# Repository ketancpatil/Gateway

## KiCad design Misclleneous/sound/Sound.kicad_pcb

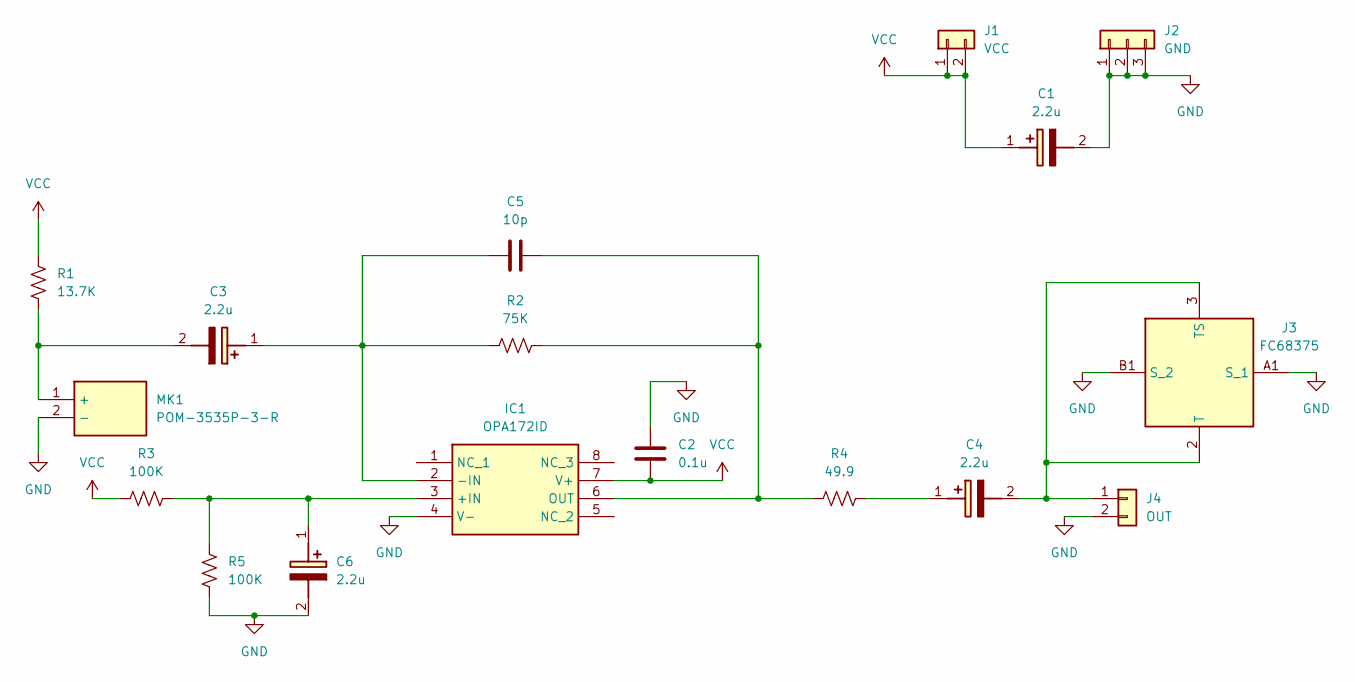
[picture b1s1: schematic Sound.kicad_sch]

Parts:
C1, C3, C4, C6: 2.2u; 293D225X9016A2TE3; Manufacturer_Part_Number 293D225X9016A2TE3; Mouser Part Number 74-293D225X9016A2TE3
C2: 0.1u; C_1206_3216Metric_Pad1.33x1.80mm_HandSolder
C5: 10p; C_1206_3216Metric_Pad1.33x1.80mm_HandSolder
IC1: OPA172ID; SOIC127P600X175-8N; Mouser Part Number 595-OPA172ID
J1: VCC; PinSocket_1x02_P2.54mm_Vertical
J2: GND; PinSocket_1x03_P2.54mm_Vertical
J3: FC68375; Manufacturer_Part_Number FC68375
J4: OUT; PinSocket_1x02_P2.54mm_Vertical
MK1: POM-3535P-3-R; POM3535P3R; Manufacturer_Part_Number POM-3535P-3-R; Mouser Part Number 665-POM-3535P-3-R
R1: 13.7K; R_1206_3216Metric_Pad1.30x1.75mm_HandSolder
R2: 75K; R_1206_3216Metric_Pad1.30x1.75mm_HandSolder
R3, R5: 100K; R_1206_3216Metric_Pad1.30x1.75mm_HandSolder
R4: 49.9; R_1206_3216Metric_Pad1.30x1.75mm_HandSolder

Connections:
GND: C1.2 (-), C2.2, C6.2 (-), IC1.4 (V-), J2.1, J2.2, J2.3, J3.A1 (S_1), J3.B1 (S_2), J4.2, MK1.2 (-), R5.1
unnamed: C3.1 (+), C5.2, IC1.2 (-IN), R2.1
unnamed: C3.2 (-), MK1.1 (+), R1.2
unnamed: C4.1 (+), R4.2
unnamed: C4.2 (-), J3.2 (T), J3.3 (TS), J4.1
unnamed: C6.1 (+), IC1.3 (+IN), R3.2, R5.2
unnamed: C5.1, IC1.6 (OUT), R2.2, R4.1
VCC: C1.1 (+), C2.1, IC1.7 (V+), J1.1, J1.2, R1.1, R3.1

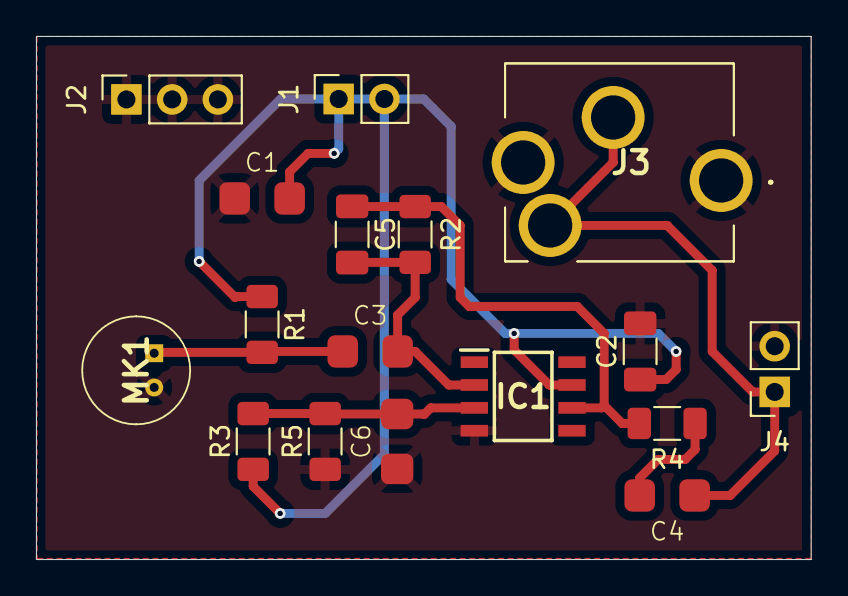
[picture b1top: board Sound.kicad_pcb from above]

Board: 2 copper layers, 43.0 x 29.1 mm, 17 parts (0 on the bottom side), 8 nets.

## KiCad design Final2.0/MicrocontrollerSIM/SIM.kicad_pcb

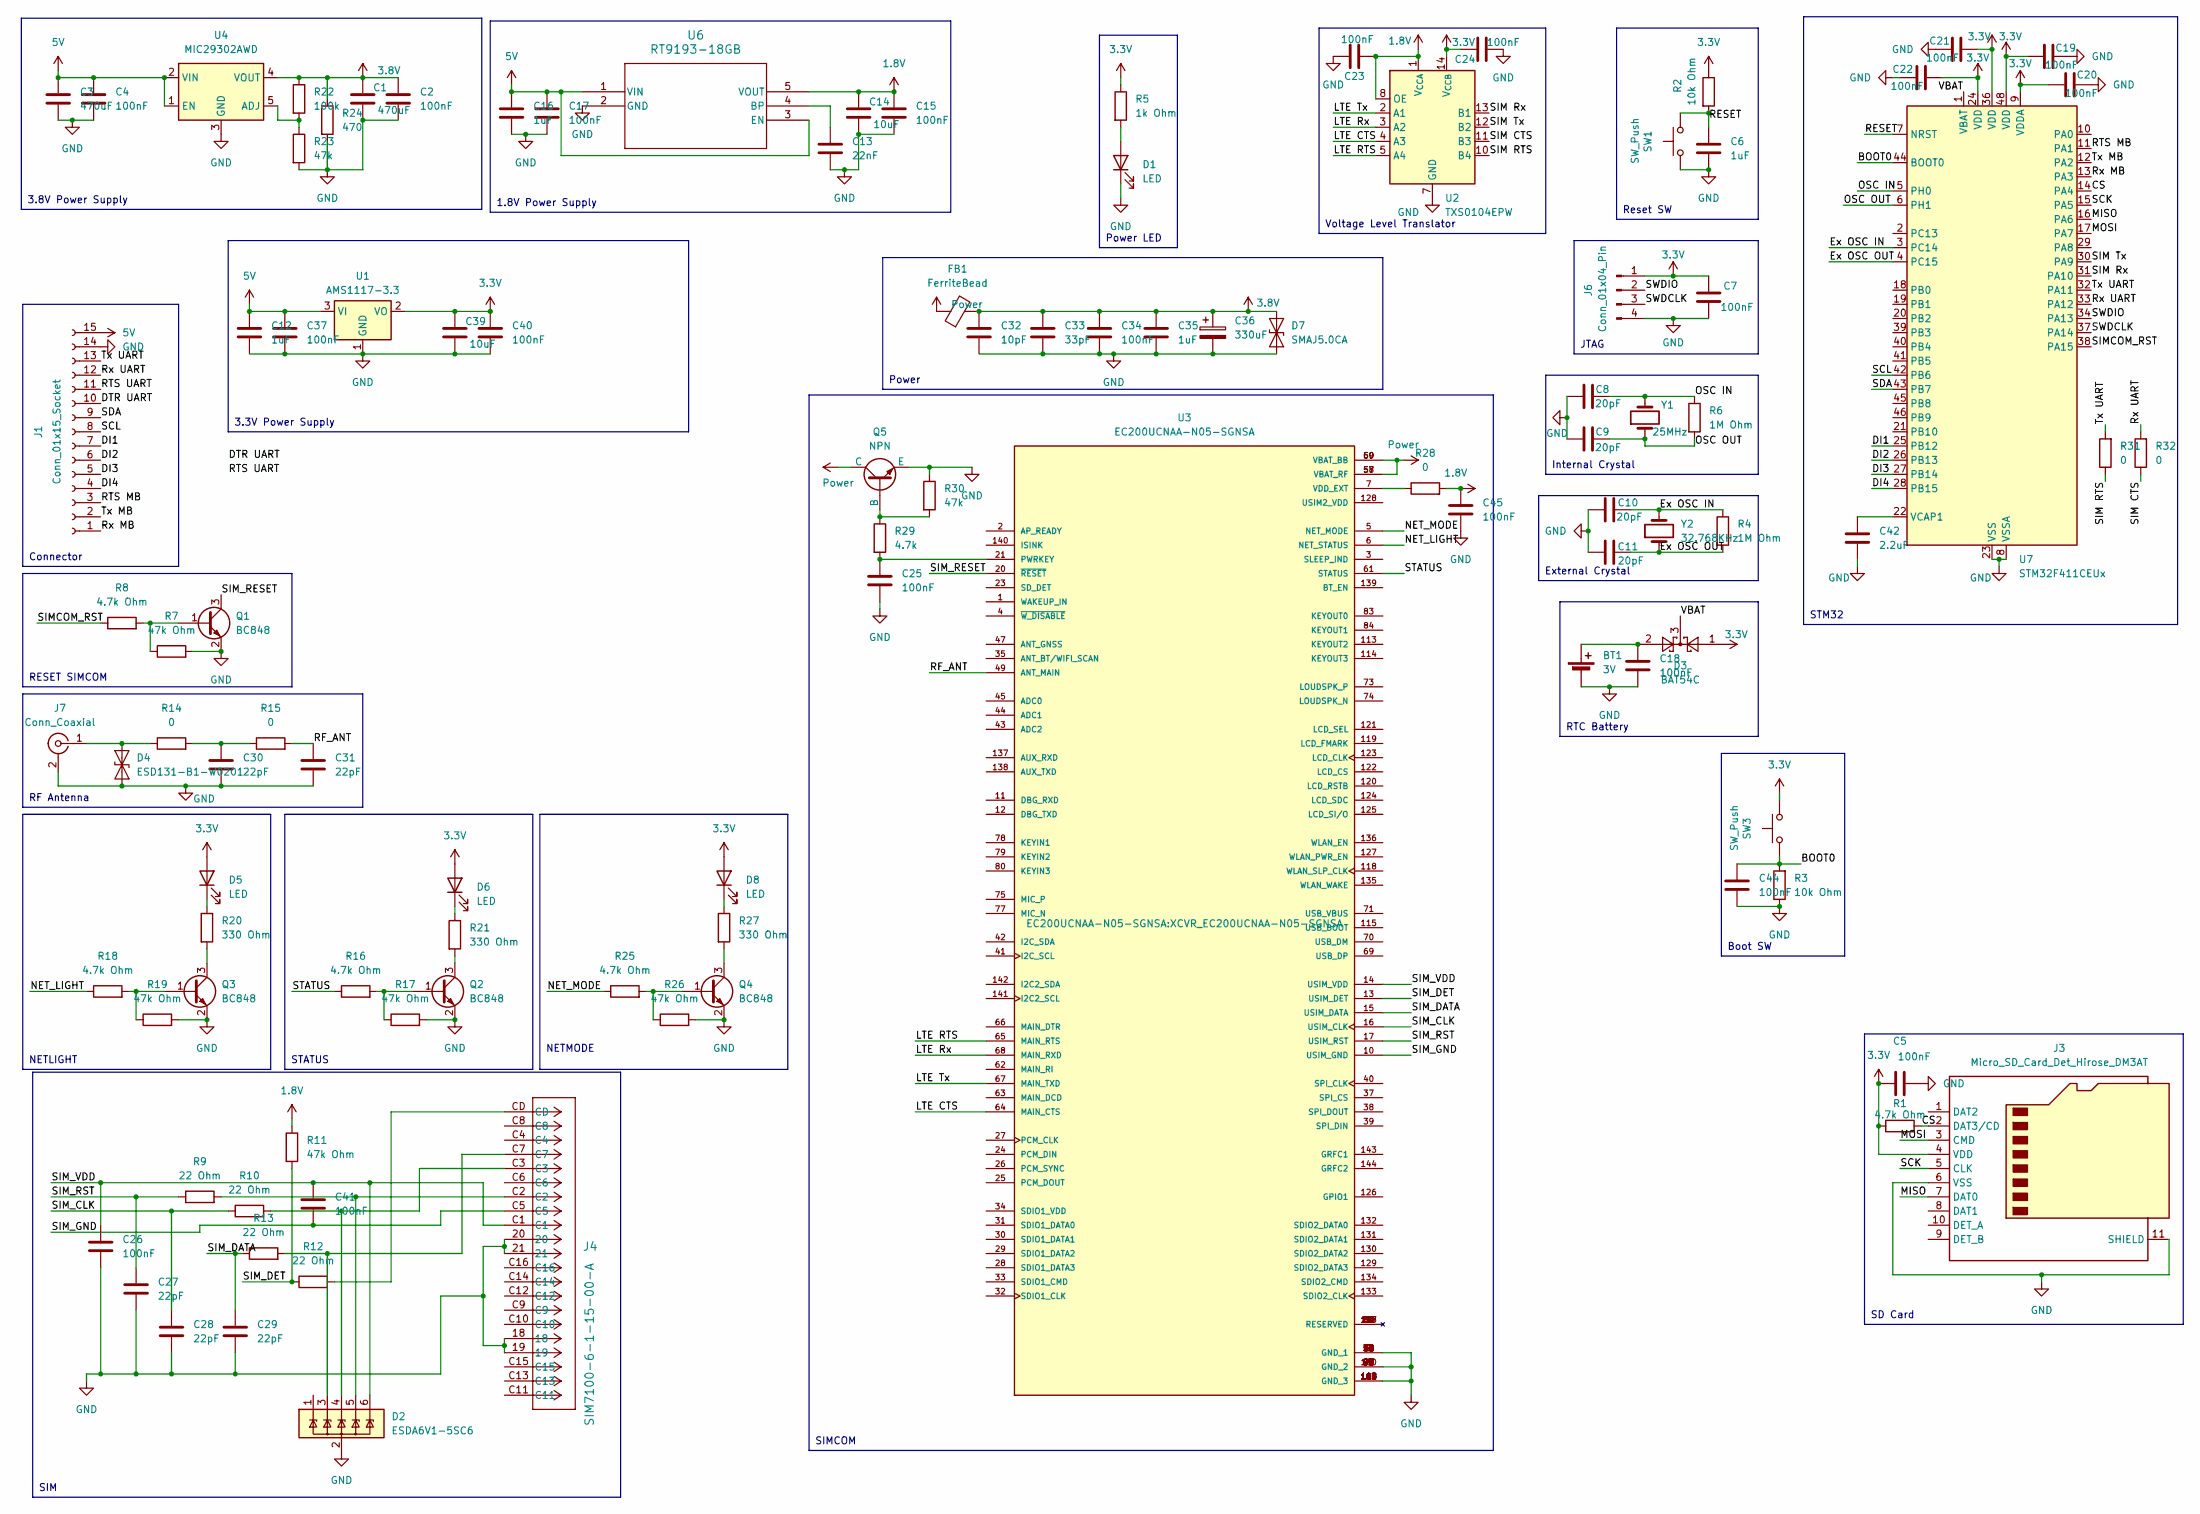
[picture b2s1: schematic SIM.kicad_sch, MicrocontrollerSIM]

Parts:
BT1: 3V; PinHeader_1x02_P2.54mm_Vertical
C1, C3: 470uF; CP_EIA-7260-15_AVX-R_Pad2.68x6.30mm_HandSolder
C2, C4, C5, C7, C15, C17, C18, C19, C20, C21, C22, C23, C24, C25, C26, C34, C37, C40, C41, C44, C45: 100nF; C_0805_2012Metric_Pad1.18x1.45mm_HandSolder
C6, C12, C16, C35: 1uF; C_0805_2012Metric_Pad1.18x1.45mm_HandSolder
C8, C9, C10, C11: 20pF; C_0805_2012Metric_Pad1.18x1.45mm_HandSolder
C13: 22nF; C_0805_2012Metric_Pad1.18x1.45mm_HandSolder
C14, C39: 10uF; C_0805_2012Metric_Pad1.18x1.45mm_HandSolder
C27, C28, C29, C30, C31: 22pF; C_0805_2012Metric_Pad1.18x1.45mm_HandSolder
C32: 10pF; C_0805_2012Metric_Pad1.18x1.45mm_HandSolder
C33: 33pF; C_0805_2012Metric_Pad1.18x1.45mm_HandSolder
C36: 330uF; CP_EIA-6032-15_Kemet-U
C42: 2.2uF; C_0805_2012Metric_Pad1.18x1.45mm_HandSolder
D1, D5, D6, D8: LED; D_0805_2012Metric_Pad1.15x1.40mm_HandSolder
D2: ESDA6V1-5SC6; SOT-23-6
D3: BAT54C; SOT-23
D4: ESD131-B1-W0201; Nexperia_DSN0603-2_0.6x0.3mm_P0.4mm
D7: SMAJ5.0CA; D_SMA
FB1: FerriteBead; Fuse_1206_3216Metric_Pad1.42x1.75mm_HandSolder
J1: Conn_01x15_Socket; PinHeader_1x15_P2.54mm_Vertical
J3: Micro_SD_Card_Det_Hirose_DM3AT; microSD_HC_Hirose_DM3AT-SF-PEJM5
J4: SIM7100-6-1-15-00-A; CONN21_-6-1-15-00-A_GCT
J6: Conn_01x04_Pin; PinSocket_1x04_P2.54mm_Vertical
J7: Conn_Coaxial; U.FL_Molex_MCRF_73412-0110_Vertical
Q1, Q2, Q3, Q4: BC848; SOT-23
Q5: NPN; SOT-23-3
R1, R8, R16, R18, R25: 4.7k Ohm; R_0805_2012Metric_Pad1.20x1.40mm_HandSolder
R2, R3: 10k Ohm; R_0805_2012Metric_Pad1.20x1.40mm_HandSolder
R4, R6: 1M Ohm; R_0805_2012Metric_Pad1.20x1.40mm_HandSolder
R5: 1k Ohm; R_0805_2012Metric_Pad1.20x1.40mm_HandSolder
R7, R11, R17, R19, R26: 47k Ohm; R_0805_2012Metric_Pad1.20x1.40mm_HandSolder
R9, R10, R12, R13: 22 Ohm; R_0805_2012Metric_Pad1.20x1.40mm_HandSolder
R14, R15, R28, R31, R32: 0; R_0805_2012Metric_Pad1.20x1.40mm_HandSolder
R20, R21, R27: 330 Ohm; R_0805_2012Metric_Pad1.20x1.40mm_HandSolder
R22: 100k; R_0805_2012Metric_Pad1.20x1.40mm_HandSolder
R23, R30: 47k; R_0805_2012Metric_Pad1.20x1.40mm_HandSolder
R24: 470; R_0805_2012Metric_Pad1.20x1.40mm_HandSolder
R29: 4.7k; R_0805_2012Metric_Pad1.20x1.40mm_HandSolder
SW1, SW3: SW_Push; SW_SPST_B3U-1000P
U1: AMS1117-3.3; SOT-223-3_TabPin2
U2: TXS0104EPW; TSSOP-14_4.4x5mm_P0.65mm
U3: EC200UCNAA-N05-SGNSA; XCVR_EC200UCNAA-N05-SGNSA; PARTREV 1.2
U4: MIC29302AWD; TO-252-5_TabPin3
U6: RT9193-18GB; SOT-23-5_RIT
U7: STM32F411CEUx; QFN-48-1EP_7x7mm_P0.5mm_EP5.6x5.6mm
Y1: 25MHz; Crystal_SMD_MicroCrystal_CC7V-T1A-2Pin_3.2x1.5mm
Y2: 32.768KHz; Crystal_SMD_2012-2Pin_2.0x1.2mm_HandSoldering

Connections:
1.8V: C14.1, C15.1, C23.2, C45.1, R11.1, R28.2, U2.1 (V_{CCA}), U2.8 (OE), U6.5 (VOUT)
3.3V: C5.1, C7.1, C19.1, C20.1, C21.2, C22.2, C24.1, C39.1, C40.1, D3.1, D5.2 (A), D6.2 (A), D8.2 (A), J3.4 (VDD), J6.1, R1.1, R2.1, R5.1, SW3.2, U1.2 (VO), U2.14 (V_{CCB}), U7.9 (VDDA), U7.24 (VDD), U7.36 (VDD), U7.48 (VDD)
3.8V: C1.1, C2.1, C32.1, C33.1, C34.1, C35.1, C36.1, D7.2 (A2), FB1.2, R22.1, R24.1, U4.4 (VOUT)
5V: C3.1, C4.1, C12.1, C16.1, C17.1, C37.1, J1.15, U1.3 (VI), U4.1 (EN), U4.2 (VIN), U6.1 (VIN), U6.3 (EN)
/BOOT0: C44.1, R3.2, SW3.1, U7.44 (BOOT0)
/CS: J3.2 (DAT3/CD), R1.2, U7.14 (PA4)
/DI1: J1.7, U7.25 (PB12)
/DI2: J1.6, U7.26 (PB13)
/DI3: J1.5, U7.27 (PB14)
/DI4: J1.4, U7.28 (PB15)
/DTR UART: J1.10
/Ex OSC IN: C10.2, R4.1, U7.3 (PC14), Y2.2
/Ex OSC OUT: C11.2, R4.2, U7.4 (PC15), Y2.1
/LTE CTS: U2.4 (A3), U3.64 (MAIN_CTS)
/LTE RTS: U2.5 (A4), U3.65 (MAIN_RTS)
/LTE Rx: U2.3 (A2), U3.68 (MAIN_RXD)
/LTE Tx: U2.2 (A1), U3.67 (MAIN_TXD)
/MISO: J3.7 (DAT0), U7.16 (PA6)
/MOSI: J3.3 (CMD), U7.17 (PA7)
/NET_LIGHT: R18.1, U3.6 (NET_STATUS)
/NET_MODE: R25.1, U3.5 (NET_MODE)
/OSC IN: C8.2, R6.1, U7.5 (PH0), Y1.2
/OSC OUT: C9.2, R6.2, U7.6 (PH1), Y1.1
/RESET: C6.1, R2.2, SW1.2, U7.7 (NRST)
/RF_ANT: C31.1, R15.2, U3.49 (ANT_MAIN)
/RTS MB: J1.3, U7.11 (PA1)
/RTS UART: J1.11
/Rx MB: J1.1, U7.13 (PA3)
/Rx UART: J1.12, R32.2, U7.33 (PA12)
/SCK: J3.5 (CLK), U7.15 (PA5)
/SCL: J1.8, U7.42 (PB6)
/SDA: J1.9, U7.43 (PB7)
/SIM CTS: R32.1, U2.11 (B3)
/SIM RTS: R31.1, U2.10 (B4)
/SIM Rx: U2.13 (B1), U7.31 (PA10)
/SIM Tx: U2.12 (B2), U7.30 (PA9)
/SIMCOM_RST: R8.1, U7.38 (PA15)
/SIM_CLK: C28.1, R10.1, U3.16 (USIM_CLK)
/SIM_DATA: C29.1, R13.1, U3.15 (USIM_DATA)
/SIM_DET: R11.2, R12.1, U3.13 (USIM_DET)
/SIM_GND: C41.2, J4.C5, U3.10 (USIM_GND)
/SIM_RESET: Q1.3 (C), U3.20 (~RESET)
/SIM_RST: C27.1, R9.1, U3.17 (USIM_RST)
/SIM_VDD: C26.1, C41.1, D2.6 (IO5), J4.C1, U3.14 (USIM_VDD)
/STATUS: R16.1, U3.61 (STATUS)
/SWDCLK: J6.3, U7.37 (PA14)
/SWDIO: J6.2, U7.34 (PA13)
/Tx MB: J1.2, U7.12 (PA2)
/Tx UART: J1.13, R31.2, U7.32 (PA11)
/VBAT: D3.3, U7.1 (VBAT)
GND: BT1.2 (-), C1.2, C2.2, C3.2, C4.2, C5.2, C6.2, C7.2, C8.1, C9.1, C10.1, C11.1, C12.2, C13.2, C14.2, C15.2, C16.2, C17.2, C18.2, C19.2, C20.2, C21.1, C22.1, C23.1, C24.2, C25.1, C26.2, C27.2, C28.2, C29.2, C30.2, C31.2, C32.2, C33.2, C34.2, C35.2, C36.2, C37.2, C39.2, C40.2, C42.2, C44.2, C45.2, D1.1 (K), D2.2 (GND), D4.2 (A2), D7.1 (A1), J1.14, J3.6 (VSS), J3.11 (SHIELD), J4.18, J4.19, J4.20, J4.21, J6.4, J7.2 (Ext), Q1.2 (E), Q2.2 (E), Q3.2 (E), Q4.2 (E), Q5.3 (E), R3.1, R7.2, R17.2, R19.2, R23.2, R24.2, R26.2, R30.1, SW1.1, U1.1 (GND), U2.7 (GND), U3.8 (GND_1), U3.9 (GND_1), U3.19 (GND_1), U3.22 (GND_1), U3.36 (GND_1), U3.46 (GND_1), U3.48 (GND_1), U3.50 (GND_1), U3.51 (GND_1), U3.52 (GND_1), U3.53 (GND_1), U3.54 (GND_1), U3.56 (GND_1), U3.72 (GND_1), U3.76 (GND_1), U3.85 (GND_2), U3.86 (GND_2), U3.87 (GND_2), U3.88 (GND_2), U3.89 (GND_2), U3.90 (GND_2), U3.91 (GND_2), U3.92 (GND_2), U3.93 (GND_2), U3.94 (GND_2), U3.95 (GND_2), U3.96 (GND_2), U3.97 (GND_2), U3.98 (GND_2), U3.99 (GND_2), U3.100 (GND_2), U3.101 (GND_3), U3.102 (GND_3), U3.103 (GND_3), U3.104 (GND_3), U3.105 (GND_3), U3.106 (GND_3), U3.107 (GND_3), U3.108 (GND_3), U3.109 (GND_3), U3.110 (GND_3), U3.111 (GND_3), U3.112 (GND_3), U4.3 (GND), U6.2 (GND), U7.8 (VSSA), U7.23 (VSS), U7.35 (VSS), U7.47 (VSS), U7.49 (VSS)
unnamed: BT1.1 (+), C18.1, D3.2
unnamed: C30.1, R14.2, R15.1
unnamed: D1.2 (A), R5.2
unnamed: D2.3 (IO2), J4.C7, R13.2
unnamed: D2.4 (IO3), J4.C3, R10.2
unnamed: D2.5 (IO4), J4.C2, R9.2
unnamed: D4.1 (A1), J7.1 (In), R14.1
unnamed: D5.1 (K), R20.1
unnamed: D6.1 (K), R21.1
unnamed: D8.1 (K), R27.1
unnamed: J4.CD, R12.2
unnamed: Q1.1 (B), R7.1, R8.2
unnamed: Q2.1 (B), R16.2, R17.1
unnamed: Q2.3 (C), R21.2
unnamed: Q3.1 (B), R18.2, R19.1
unnamed: Q3.3 (C), R20.2
unnamed: Q4.1 (B), R25.2, R26.1
unnamed: Q4.3 (C), R27.2
unnamed: Q5.2 (B), R29.1, R30.2
unnamed: C25.2, R29.2, U3.21 (PWRKEY)
unnamed: R28.1, U3.7 (VDD_EXT)
unnamed: R22.2, R23.1, U4.5 (ADJ)
unnamed: C13.1, U6.4 (BP)
unnamed: C42.1, U7.22 (VCAP1)
Power: FB1.1, Q5.1 (C), U3.57 (VBAT_RF), U3.58 (VBAT_RF), U3.59 (VBAT_BB), U3.60 (VBAT_BB)

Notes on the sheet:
1.8V Power Supply
Power LED
External Crystal
JTAG
SIMCOM
RF Antenna
3.3V Power Supply
Connector
Reset SW
NETLIGHT
Internal Crystal
STM32
RESET SIMCOM
SD Card
NETMODE
SIM
STATUS
Voltage Level Translator
Boot SW
RTC Battery
3.8V Power Supply
Power

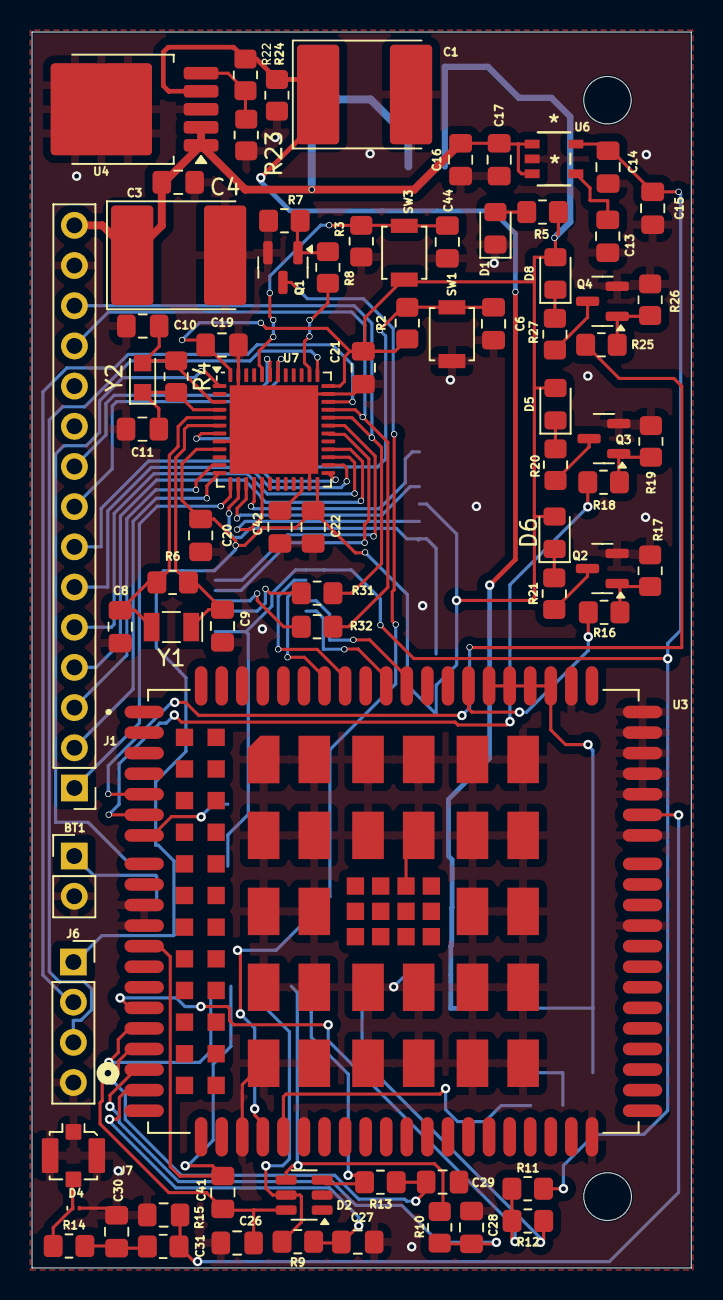
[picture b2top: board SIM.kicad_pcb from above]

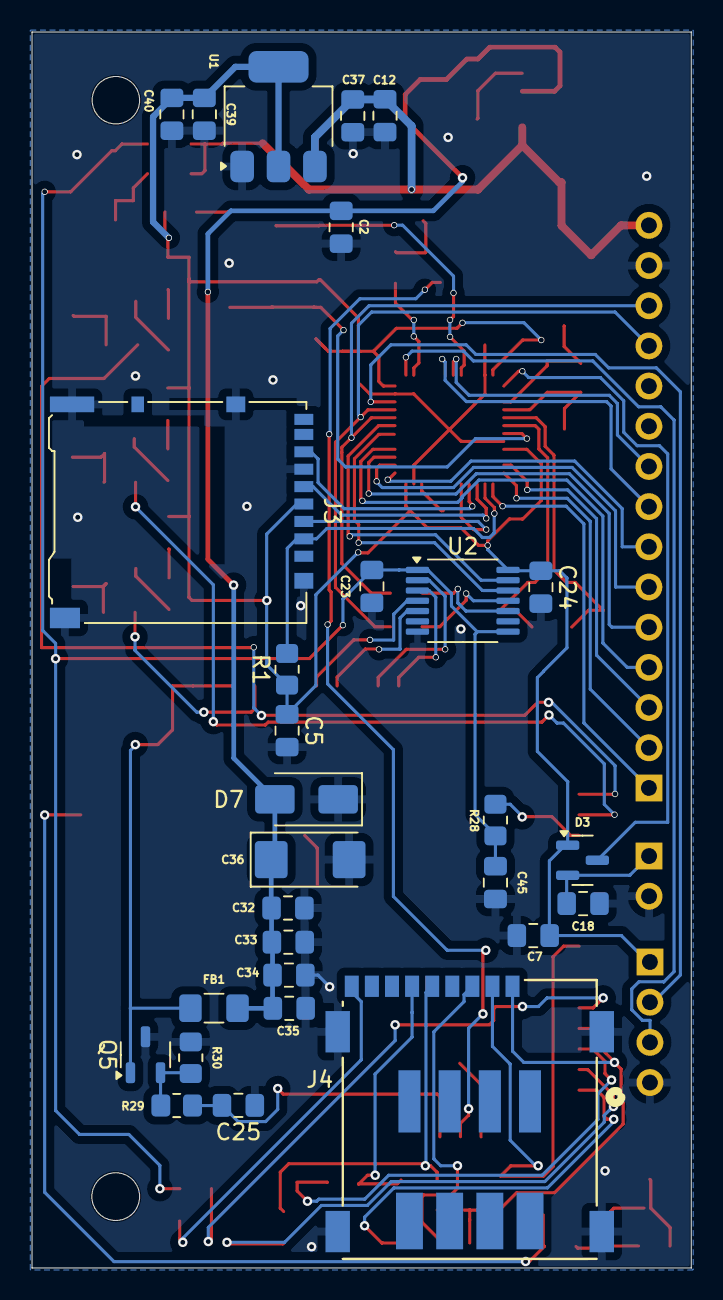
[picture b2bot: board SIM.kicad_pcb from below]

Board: 2 copper layers, 41.7 x 78.1 mm, 105 parts (29 on the bottom side), 74 nets.

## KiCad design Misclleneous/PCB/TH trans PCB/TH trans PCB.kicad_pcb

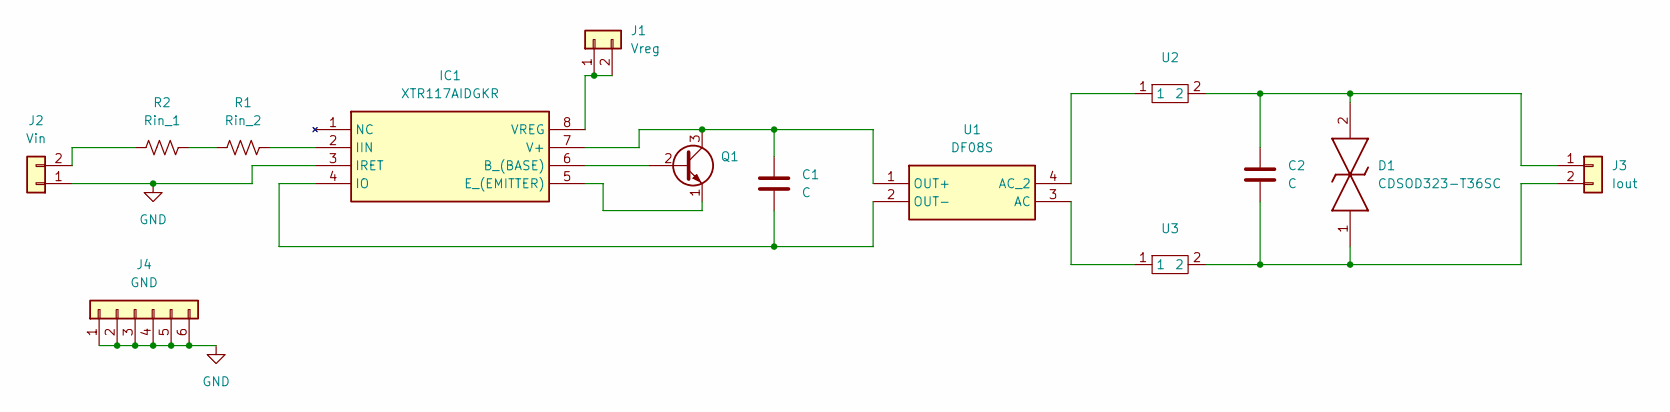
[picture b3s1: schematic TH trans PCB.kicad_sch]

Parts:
C1, C2: C; C_1206_3216Metric_Pad1.33x1.80mm_HandSolder
D1: CDSOD323-T36SC; SOD2513X114N; Mouser Part Number 652-CDSOD323-T36SC
IC1: XTR117AIDGKR; SOP65P490X110-8N; Mouser Part Number 595-XTR117AIDGKR
J1: Vreg; PinHeader_1x02_P2.54mm_Vertical
J2: Vin; PhoenixContact_MCV_1,5_2-G-5.08_1x02_P5.08mm_Vertical
J3: Iout; PhoenixContact_MCV_1,5_2-G-5.08_1x02_P5.08mm_Vertical
J4: GND; PinHeader_1x06_P2.54mm_Vertical
Q1: 2N2219; FCX690B
R1: Rin_2; R_1206_3216Metric_Pad1.30x1.75mm_HandSolder
R2: Rin_1; R_1206_3216Metric_Pad1.30x1.75mm_HandSolder
U1: DF08S; SOT508P985X260-4N; Mouser Part Number 512-DF08S
U2, U3: FB MH3225

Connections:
GND: IC1.3 (IRET), J2.1, J4.1, J4.2, J4.3, J4.4, J4.5, J4.6
unnamed: IC1.6 (B_(BASE)), Q1.2 (B)
unnamed: IC1.5 (E_(EMITTER)), Q1.1 (E)
unnamed: IC1.2 (IIN), R1.2
unnamed: C1.2, IC1.4 (IO), U1.2 (OUT-)
unnamed: C1.1, IC1.7 (V+), Q1.3 (C), U1.1 (OUT+)
unnamed: IC1.8 (VREG), J1.1, J1.2
unnamed: J2.2, R2.1
unnamed: C2.1, D1.2, J3.1, U2.2
unnamed: C2.2, D1.1, J3.2, U3.2
unnamed: R1.1, R2.2
unnamed: U1.3 (AC), U3.1
unnamed: U1.4 (AC_2), U2.1

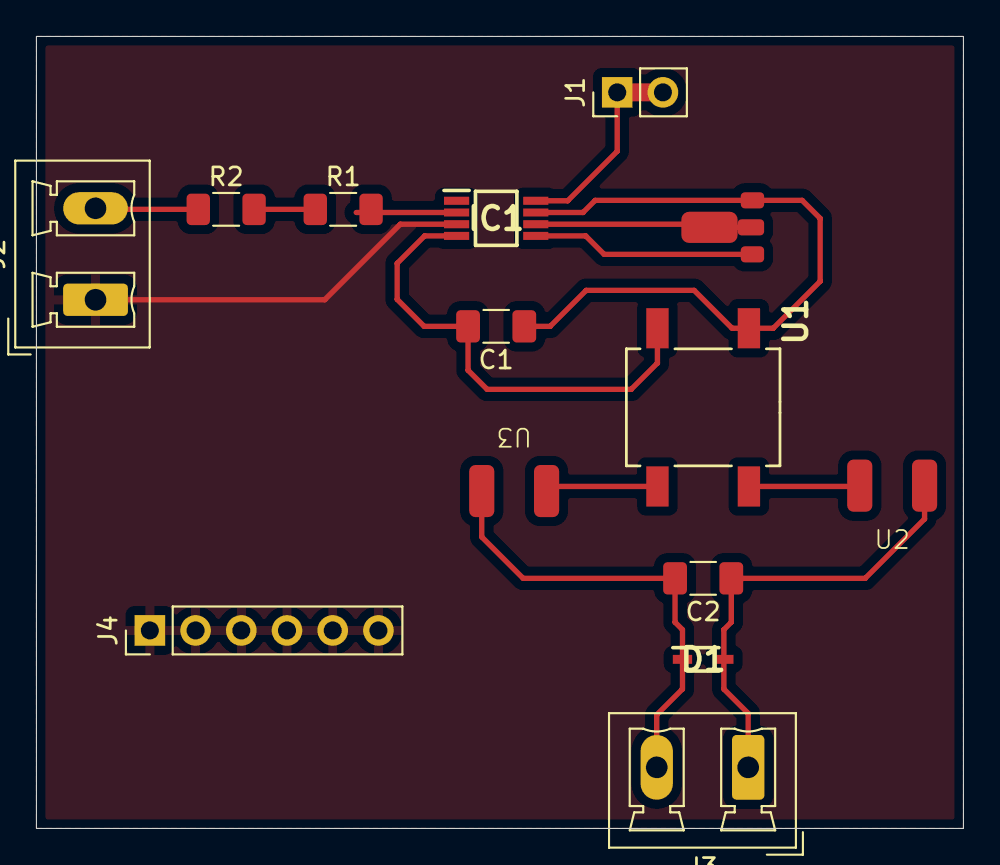
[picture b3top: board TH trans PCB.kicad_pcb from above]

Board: 2 copper layers, 51.5 x 44.0 mm, 14 parts (0 on the bottom side), 13 nets.

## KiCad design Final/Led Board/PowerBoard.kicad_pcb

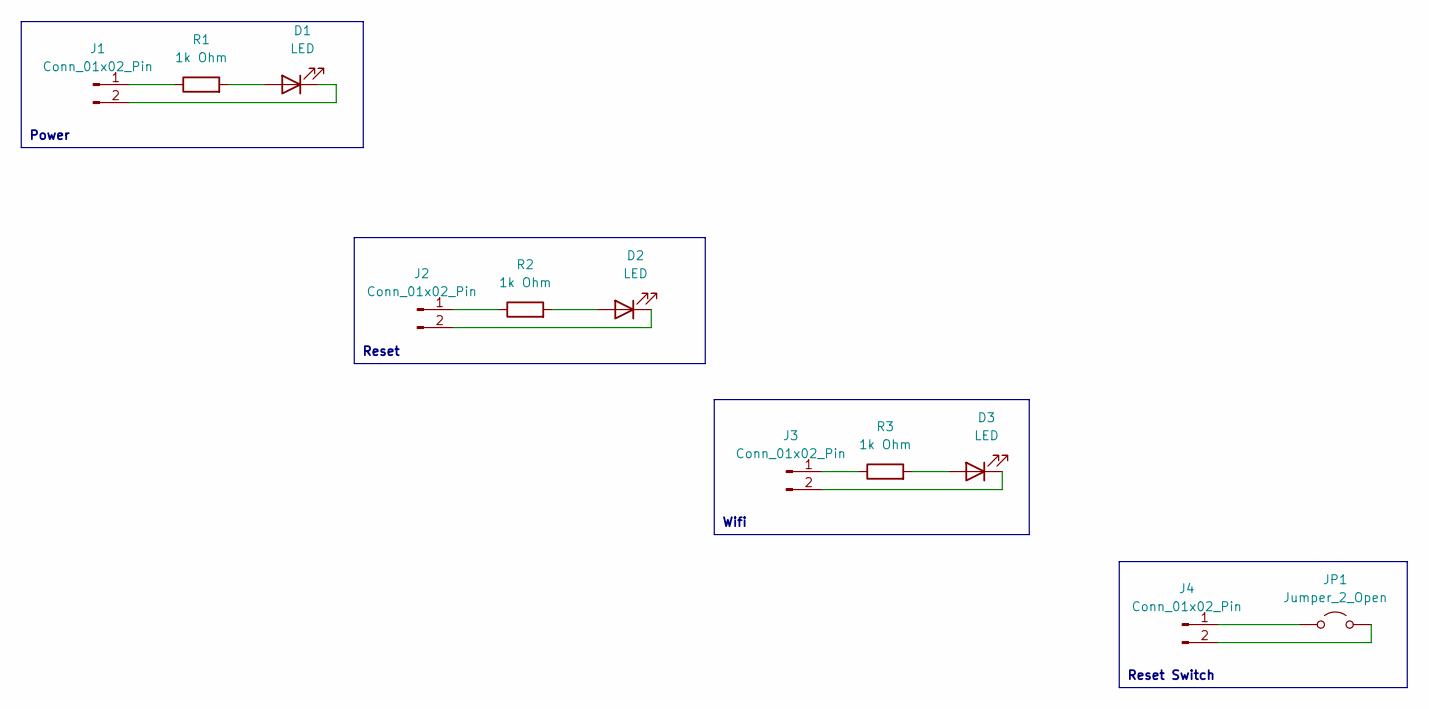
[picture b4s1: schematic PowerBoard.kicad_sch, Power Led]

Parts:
D1, D2, D3: LED; LED_D3.0mm_Clear
J1, J2, J3, J4: Conn_01x02_Pin; JST_XH_B2B-XH-A_1x02_P2.50mm_Vertical
JP1: Jumper_2_Open; SW_SPST_CK_RS282G05A3
R1, R2, R3: 1k Ohm; R_0805_2012Metric_Pad1.20x1.40mm_HandSolder

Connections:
unnamed: D1.2 (A), R1.2
unnamed: D1.1 (K), J1.2
unnamed: D2.2 (A), R2.2
unnamed: D2.1 (K), J2.2
unnamed: D3.2 (A), R3.2
unnamed: D3.1 (K), J3.2
unnamed: J1.1, R1.1
unnamed: J2.1, R2.1
unnamed: J3.1, R3.1
unnamed: J4.1, JP1.1 (A)
unnamed: J4.2, JP1.2 (B)

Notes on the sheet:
Wifi
Reset
Power
Reset Switch

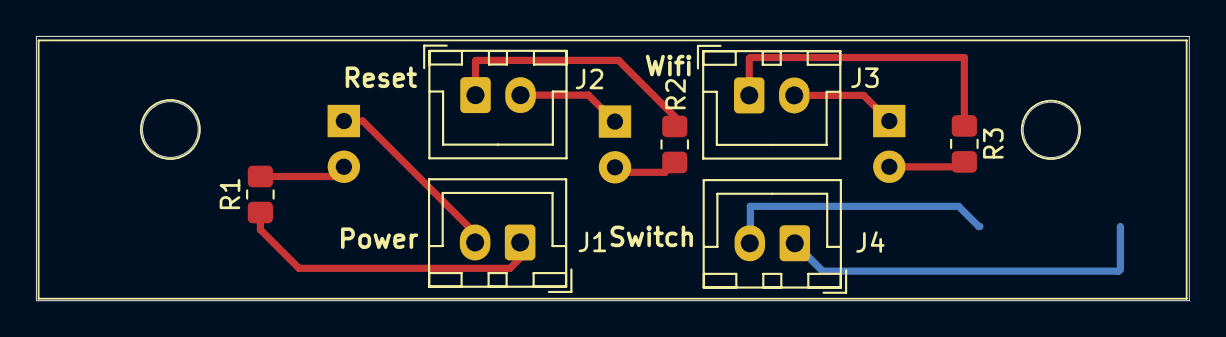
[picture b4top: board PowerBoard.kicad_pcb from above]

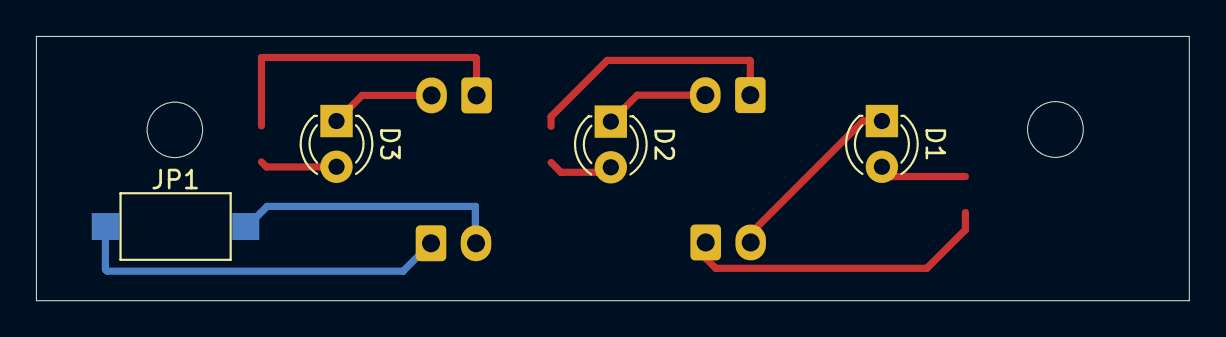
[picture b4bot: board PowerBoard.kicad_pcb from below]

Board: 2 copper layers, 64.1 x 14.7 mm, 11 parts (4 on the bottom side), 11 nets.

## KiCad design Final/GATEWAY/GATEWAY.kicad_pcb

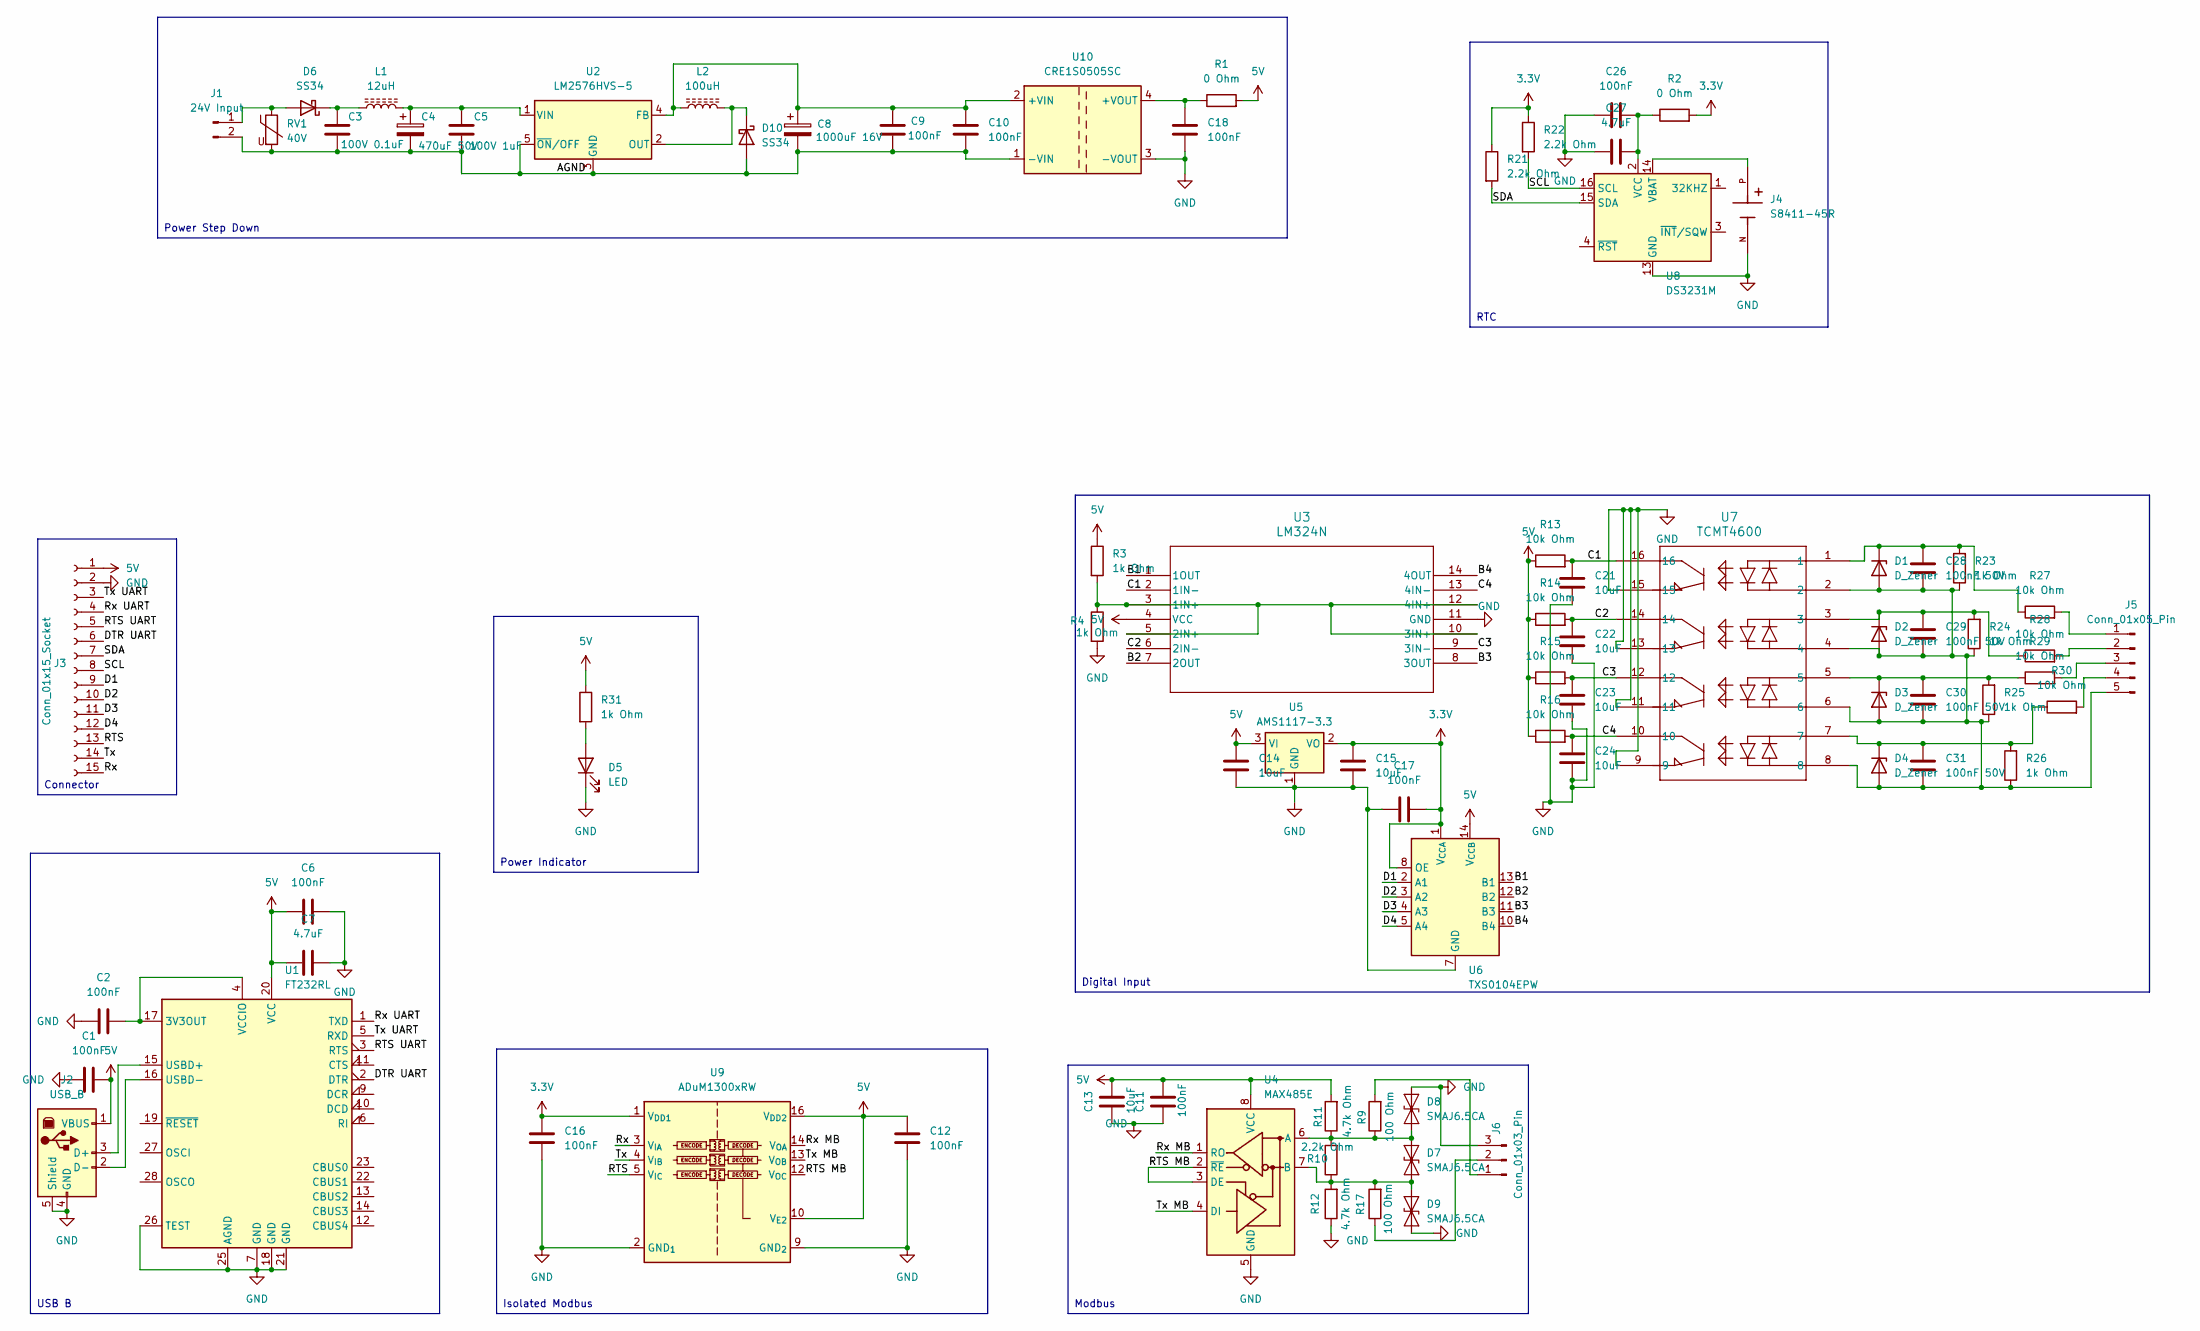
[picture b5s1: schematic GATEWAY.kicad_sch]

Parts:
C1, C2, C6, C9, C10, C11, C12, C16, C17, C18, C26: 100nF; C_0805_2012Metric_Pad1.18x1.45mm_HandSolder
C3: 100V 0.1uF; C_Rect_L7.0mm_W2.5mm_P5.00mm
C4: 470uF 50V; CP_Radial_D10.0mm_P5.00mm
C5: 100V 1uF; C_Rect_L10.3mm_W5.0mm_P7.50mm_MKS4
C7, C27: 4.7uF; C_0805_2012Metric_Pad1.18x1.45mm_HandSolder
C8: 1000uF 16V; CP_Radial_D10.0mm_P5.00mm
C13, C14, C15, C21, C22, C23, C24: 10uF; C_0805_2012Metric_Pad1.18x1.45mm_HandSolder
C28, C29, C30, C31: 100nF 50V; C_0805_2012Metric_Pad1.18x1.45mm_HandSolder
D1, D2, D3, D4: D_Zener; D_MicroMELF_Handsoldering
D5: LED; LED_0805_2012Metric_Pad1.15x1.40mm_HandSolder
D6, D10: SS34; D_SMA
D7, D8, D9: SMAJ6.5CA; D_SMA
J1: 24V Input; TerminalBlock_Phoenix_MKDS-3-2-5.08_1x02_P5.08mm_Horizontal
J2: USB_B; USB_B_OST_USB-B1HSxx_Horizontal
J3: Conn_01x15_Socket; PinSocket_1x15_P2.54mm_Vertical
J4: S8411-45R; HARWIN_S8411-45R; PARTREV 4
J5: Conn_01x05_Pin; TerminalBlock_Phoenix_MKDS-3-5-5.08_1x05_P5.08mm_Horizontal
J6: Conn_01x03_Pin; TerminalBlock_Phoenix_MKDS-3-3-5.08_1x03_P5.08mm_Horizontal
L1: 12uH; L_Vishay_IHLP-5050
L2: 100uH; L_Vishay_IHLP-5050
R1, R2: 0 Ohm; R_0805_2012Metric_Pad1.20x1.40mm_HandSolder
R3, R4, R23, R24, R25, R26, R31: 1k Ohm; R_0805_2012Metric_Pad1.20x1.40mm_HandSolder
R9, R17: 100 Ohm; R_0805_2012Metric_Pad1.20x1.40mm_HandSolder
R10, R21, R22: 2.2k Ohm; R_0805_2012Metric_Pad1.20x1.40mm_HandSolder
R11, R12: 4.7k Ohm; R_0805_2012Metric_Pad1.20x1.40mm_HandSolder
R13, R14, R15, R16, R27, R28, R29, R30: 10k Ohm; R_0805_2012Metric_Pad1.20x1.40mm_HandSolder
RV1: 40V; RV_Disc_D9mm_W3.9mm_P5mm
U1: FT232RL; SSOP-28_5.3x10.2mm_P0.65mm
U2: LM2576HVS-5; TO-263-5_TabPin3
U3: LM324N; SOIC-14_3.9x8.7mm_P1.27mm
U4: MAX485E; SOIC-8_3.9x4.9mm_P1.27mm
U5: AMS1117-3.3; SOT-223-3_TabPin2
U6: TXS0104EPW; TSSOP-14_4.4x5mm_P0.65mm
U7: TCMT4600; SOP-16_4.55x10.3mm_P1.27mm
U8: DS3231M; SOIC-16W_7.5x10.3mm_P1.27mm
U9: ADuM1300xRW; SOIC-16W_7.5x10.3mm_P1.27mm
U10: CRE1S0505SC; Converter_DCDC_Murata_CRE1xxxxxxSC_THT

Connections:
3.3V: C15.1, C16.1, C17.2, R2.2, R21.1, R22.1, U5.2 (VO), U6.1 (V_{CCA}), U6.8 (OE), U9.1 (V_{DD1})
5V: C1.2, C6.1, C7.1, C11.2, C12.1, C13.2, C14.1, J2.1 (VBUS), J3.1, R1.2, R3.1, R11.2, R13.1, R14.1, R15.1, R16.1, R31.1, U1.20 (VCC), U3.4 (VCC), U4.8 (VCC), U5.3 (VI), U6.14 (V_{CCB}), U9.10 (V_{E2}), U9.16 (V_{DD2})
/AGND: C3.2, C4.2, C5.2, C8.2, C9.2, C10.2, D10.2 (A), J1.2, RV1.2, U2.3 (GND), U2.5 (~ON/OFF), U10.1 (-VIN)
/B1: U3.1 (1OUT), U6.13 (B1)
/B2: U3.7 (2OUT), U6.12 (B2)
/B3: U3.8 (3OUT), U6.11 (B3)
/B4: U3.14 (4OUT), U6.10 (B4)
/C1: C21.1, R13.2, U3.2 (1IN-), U7.16
/C2: C22.1, R14.2, U3.6 (2IN-), U7.14
/C3: C23.1, R15.2, U3.9 (3IN-), U7.12
/C4: C24.1, R16.2, U3.13 (4IN-), U7.10
/D1: J3.9, U6.2 (A1)
/D2: J3.10, U6.3 (A2)
/D3: J3.11, U6.4 (A3)
/D4: J3.12, U6.5 (A4)
/DTR UART: J3.6, U1.2 (DTR)
/RTS: J3.13, U9.5 (V_{IC})
/RTS MB: U4.2 (~RE), U4.3 (DE), U9.12 (V_{OC})
/RTS UART: J3.5, U1.3 (RTS)
/Rx: J3.15, U9.3 (V_{IA})
/Rx MB: U4.1 (RO), U9.14 (V_{OA})
/Rx UART: J3.4, U1.1 (TXD)
/SCL: J3.8, R22.2, U8.16 (SCL)
/SDA: J3.7, R21.2, U8.15 (SDA)
/Tx: J3.14, U9.4 (V_{IB})
/Tx MB: U4.4 (DI), U9.13 (V_{OB})
/Tx UART: J3.3, U1.5 (RXD)
GND: C1.1, C2.1, C6.2, C7.2, C11.1, C12.2, C13.1, C14.2, C15.2, C16.2, C17.1, C18.2, C21.2, C22.2, C23.2, C24.2, C26.2, C27.2, D5.1 (K), D8.2 (A2), D9.1 (A1), J2.4 (GND), J2.5 (Shield), J3.2, J4.N, J6.3, R4.2, R12.1, U1.7 (GND), U1.18 (GND), U1.21 (GND), U1.25 (AGND), U1.26 (TEST), U3.11 (GND), U4.5 (GND), U5.1 (GND), U6.7 (GND), U7.9, U7.11, U7.13, U7.15, U8.5 (GND), U8.6 (GND), U8.7 (GND), U8.8 (GND), U8.9 (GND), U8.10 (GND), U8.11 (GND), U8.12 (GND), U8.13 (GND), U9.2 (GND_{1}), U9.8 (GND_{1}), U9.9 (GND_{2}), U9.15 (GND_{2}), U10.3 (-VOUT)
unnamed: C28.2, C29.2, C30.2, C31.2, D1.2 (A), D2.2 (A), D3.2 (A), D4.2 (A), J5.5, R23.1, R24.1, R25.1, R26.1, U7.2, U7.4, U7.6, U7.8
unnamed: C28.1, D1.1 (K), R23.2, R27.1, U7.1
unnamed: C29.1, D2.1 (K), R24.2, R28.1, U7.3
unnamed: C30.1, D3.1 (K), R25.2, R29.1, U7.5
unnamed: C31.1, D4.1 (K), R26.2, R30.1, U7.7
unnamed: D5.2 (A), R31.2
unnamed: D6.2 (A), J1.1, RV1.1
unnamed: C3.1, D6.1 (K), L1.1
unnamed: D7.1 (A1), D9.2 (A2), R10.1, R12.2, R17.2, U4.7 (B)
unnamed: D7.2 (A2), D8.1 (A1), R9.1, R10.2, R11.1, U4.6 (A)
unnamed: D10.1 (K), L2.2, U2.2 (OUT)
unnamed: J2.3 (D+), U1.15 (USBD+)
unnamed: J2.2 (D-), U1.16 (USBD-)
unnamed: J5.1, R27.2
unnamed: J5.2, R28.2
unnamed: J5.3, R29.2
unnamed: J5.4, R30.2
unnamed: J6.1, R9.2
unnamed: J6.2, R17.1
unnamed: C2.2, U1.4 (VCCIO), U1.17 (3V3OUT)
unnamed: C4.1, C5.1, L1.2, U2.1 (VIN)
unnamed: R3.2, R4.1, U3.3 (1IN+), U3.5 (2IN+), U3.10 (3IN+), U3.12 (4IN+)
unnamed: J4.P, U8.14 (VBAT)
unnamed: C26.1, C27.1, R2.1, U8.2 (VCC)
unnamed: C8.1, C9.1, C10.1, L2.1, U2.4 (FB), U10.2 (+VIN)
unnamed: C18.1, R1.1, U10.4 (+VOUT)

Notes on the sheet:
Connector
Digital Input
Power Step Down
RTC
USB B
Power Indicator
Isolated Modbus
Modbus
